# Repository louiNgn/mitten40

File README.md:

# mitten40 
## An ortholinear keyboard with a joystick!

The mitten40 is a 46-key, split-spacebar ortholinear keyboard with a customizable OLED screen and joystick.

### PCB Render

### PCB Layout

### Schematic

# key layout

# firmware
The mitten40 utilizes [QMK firmware](https://qmk.fm/) 

Expect coming changes to C scripts seen in the project, it's untested currently!

# case

The mitten40 utilizes a 3D printed gasket-mount case secured with M3 heat set inserts and screws.

# build guide (TO BE UPDATED ONCE I GET MY HANDS ON IT)
[View bills of materials here!](BOMs)

PCB SMD components: Options include hotplate/hot air soldering at home, assembly by a third-party service (JLCPCB is my choice), or, if you're cracked enough, hand soldering with a soldering iron.

###### FOR THE ASSEMBLY .CSV GO [HERE](production/BOM_PCBAssembly.csv)

|Designator                                                                                                                                                                                                                 |Footprint                              |Quantity|Value                      |LCSC Part #|
|---------------------------------------------------------------------------------------------------------------------------------------------------------------------------------------------------------------------------|---------------------------------------|--------|---------------------------|-----------|
|C1, C2, C3, C5, C8                                                                                                                                                                                                         |402                                    |5       |100nF                      |C60474     |
|C10, C11, C7                                                                                                                                                                                                               |402                                    |3       |1uF                        |C29266     |
|C4, C9                                                                                                                                                                                                                     |402                                    |2       |4.7uF                      |C368809    |
|C6                                                                                                                                                                                                                         |402                                    |1       |10nF                       |C15195     |
|D1, D10, D11, D12, D13, D14, D15, D16, D17, D18, D19, D2, D20, D21, D22, D23, D24, D25, D26, D27, D28, D29, D3, D30, D31, D32, D33, D34, D35, D36, D37, D38, D39, D4, D40, D41, D42, D43, D44, D45, D46, D5, D6, D7, D8, D9|D_SOD-123                              |46      |D                          |C2972760   |
|F1                                                                                                                                                                                                                         |603                                    |1       |500mA                      |C136327    |
|J3                                                                                                                                                                                                                         |USB_C_Receptacle_HCTL_HC-TYPE-C-16P-01A|1       |USB_C_Receptacle_USB2.0_16P|C2765186   |
|R1                                                                                                                                                                                                                         |402                                    |1       |10k                        |C60490     |
|R2, R3                                                                                                                                                                                                                     |402                                    |2       |5.1k                       |C25905     |
|SW0                                                                                                                                                                                                                        |SW_SPST_TL3342                         |1       |SW_Push                    |C2886898   |
|U1                                                                                                                                                                                                                         |LQFP-48_7x7mm_P0.5mm                   |1       |STM32F072CBT6              |C81720     |
|U2                                                                                                                                                                                                                         |SOT-23-6                               |1       |USBLC6-2SC6                |C7519      |
|U3                                                                                                                                                                                                                         |SOT-23-3                               |1       |XC6206P332MR-MS            |C5252899   |

Before continuing, flash QMK firmware on to the keyboard, and use a pair of conductive tweezers to test the PCB for any issues (firmware error, damaged PCB, unresponsive through-hole pins, etc...), and resolve any issues that arises (which may include reordering your PCB).

PCB through-hole components: With sufficient flux and a soldering iron, solder Cherry-MX compatible switches, joystick, and OLED screen through their respective through-hole components. Optionally, solder a 4-pin socket through the OLED screen footprint if you want easily-swappable screens/afraid of damaging the screen when soldering directly.
#### IMPORTANT: REMEMBER TO MOUNT SWITCHES ON TO THE PLATE BEFORE SANDWICHING THEM TO THE PCB AND SOLDERING THEM!!!!

|Designator                                                                                                                                                                                                                 |Part                                   |Quantity|Additional notes           |
|---------------------------------------------------------------------------------------------------------------------------------------------------------------------------------------------------------------------------|---------------------------------------|--------|---------------------------|
|SW1-46                                                                                                                                                                                                                     |MX-Compatible Switches                 |46      |                           |
|SW48                                                                                                                                                                                                                       |PS2-style analog joystick              |1       |Something similar to the [SparkFun joystick](https://www.sparkfun.com/thumb-joystick.html) should work|
|J2                                                                                                                                                                                                                         |0.91" 4-pin OLED Display               |        |Solder sockets on if you want|

Case assembly:
+ Assuming you've mounted the switches on to the plate and the PCB before soldering, begin attaching foam gaskets you've bought on to the top of the small "fins" extruded around the plate on both sides, trimming excess material where necessary to ensure a tight fit.
+ Use your soldering iron, and optionally a heat-set insert press for more precision, push the M3 heat set inserts into their respective holes in the top housing of the keyboard case, before letting everything cool down. (NOTE: DO NOT PRESS TOO FAR AS IT MIGHT GO THROUGH THE ENTIRE HOUSING)
+ Sandwich the PCB-plate between the top and the bottom housing, ensuring the entire contraption is sitting flush in between them.
+ Use M3 screws you've bought to bolt everything together from the bottom housing, tightening it too hard may lead to the housings cracking so please avoid that.
+ Finally, attach the anti-slip nubs on to the bottom of the case in their respective nub holes, and wait for it to set into the PCB before using.

| Part                               | Quantity                  | Additional notes                                                                        | Estimated total costs (may be pricier outside of my country | Links I used |
|------------------------------------|---------------------------|-----------------------------------------------------------------------------------------|-------------------------------------------------------------|--------------|
| Heat-set inserts (M3 * 4 * 4.5)    | 8                         |                                                                                         | $0.60                                                       | [Shopee](https://shopee.vn/30-%E1%BB%90c-c%E1%BA%A5y-nhi%E1%BB%87t-%C4%91%E1%BB%93ng-M1.4-M2-M2.5-M3-M4-M5-M6-T%C3%A1n-Ren-C%E1%BA%A5y-G%E1%BA%AFn-Nh%E1%BB%B1a-Voron-c%E1%BA%A5y-nh%E1%BB%B1a-ecu-c%E1%BA%A5y-%C4%91%E1%BB%93ng-i.213254391.20175149003?extraParams=%7B%22display_model_id%22%3A240042089992%2C%22model_selection_logic%22%3A3%7D)       |
| Threaded Socket Head Cap M3 Screws | 8                         | A shank around 16mm should work, though it *might* go up to 18mm. Proceed with caution. | $0.80                                                       | [Shopee](https://shopee.vn/20C%C3%A1i-Bulong-%E1%BB%91c-Tr%E1%BB%A5-L%E1%BB%A5c-Gi%C3%A1c-trong-M3-M4-M5-M6-M8-inox304-i.801113520.42860368235?extraParams=%7B%22display_model_id%22%3A360010588761%2C%22model_selection_logic%22%3A3%7D&image_ids=vn-11134207-7ras8-mcn8v44lo7z006)       |
| 70mm * 3.5mm * 2mm Poron Foam Gaskets  | 12                        | 2mms of thickness, cut down if need be.                                                 | $6.39                                                            | [Shopee](https://shopee.vn/B%E1%BB%99-5-Mi%E1%BA%BFng-Foam-Gasket-Poron-Thay-Th%E1%BA%BF-Cho-B%C3%A0n-Ph%C3%ADm-C%C6%A1-Gasket-Mount-Yeti-Mech-i.1065372747.46601199338?extraParams=%7B%22display_model_id%22%3A366464970958%2C%22model_selection_logic%22%3A3%7D&image_ids=vn-11134207-81ztc-ms56gdwgudjb02)       |
| 3M SJ5302 Anti-stick nubs          | 4                         |                                                                                         | $1.20                                                       | [Shopee](https://shopee.vn/30-N%C3%BAt-%C4%90%E1%BB%87m-Ch%E1%BB%91ng-v%E1%BB%A1-%C4%90i%E1%BB%87n-Tho%E1%BA%A1i-3M-SJ5302-(N%C3%BAt-V%C3%B2m-C%E1%BA%A7u)-v%C3%A0-20-N%C3%BAt-JS5312-(N%C3%BAt-D%E1%BA%B9t)-i.13893035.2055224981?extraParams=%7B%22display_model_id%22%3A223329961555%2C%22model_selection_logic%22%3A3%7D)       |
| Filament (PLA)                     | ~270+ grams or ~90m (PLA) | May vary with different filaments and print settings                                    | ~$5.40                                                      | Self-funded and printed (I have a lot of filament lying around)             |

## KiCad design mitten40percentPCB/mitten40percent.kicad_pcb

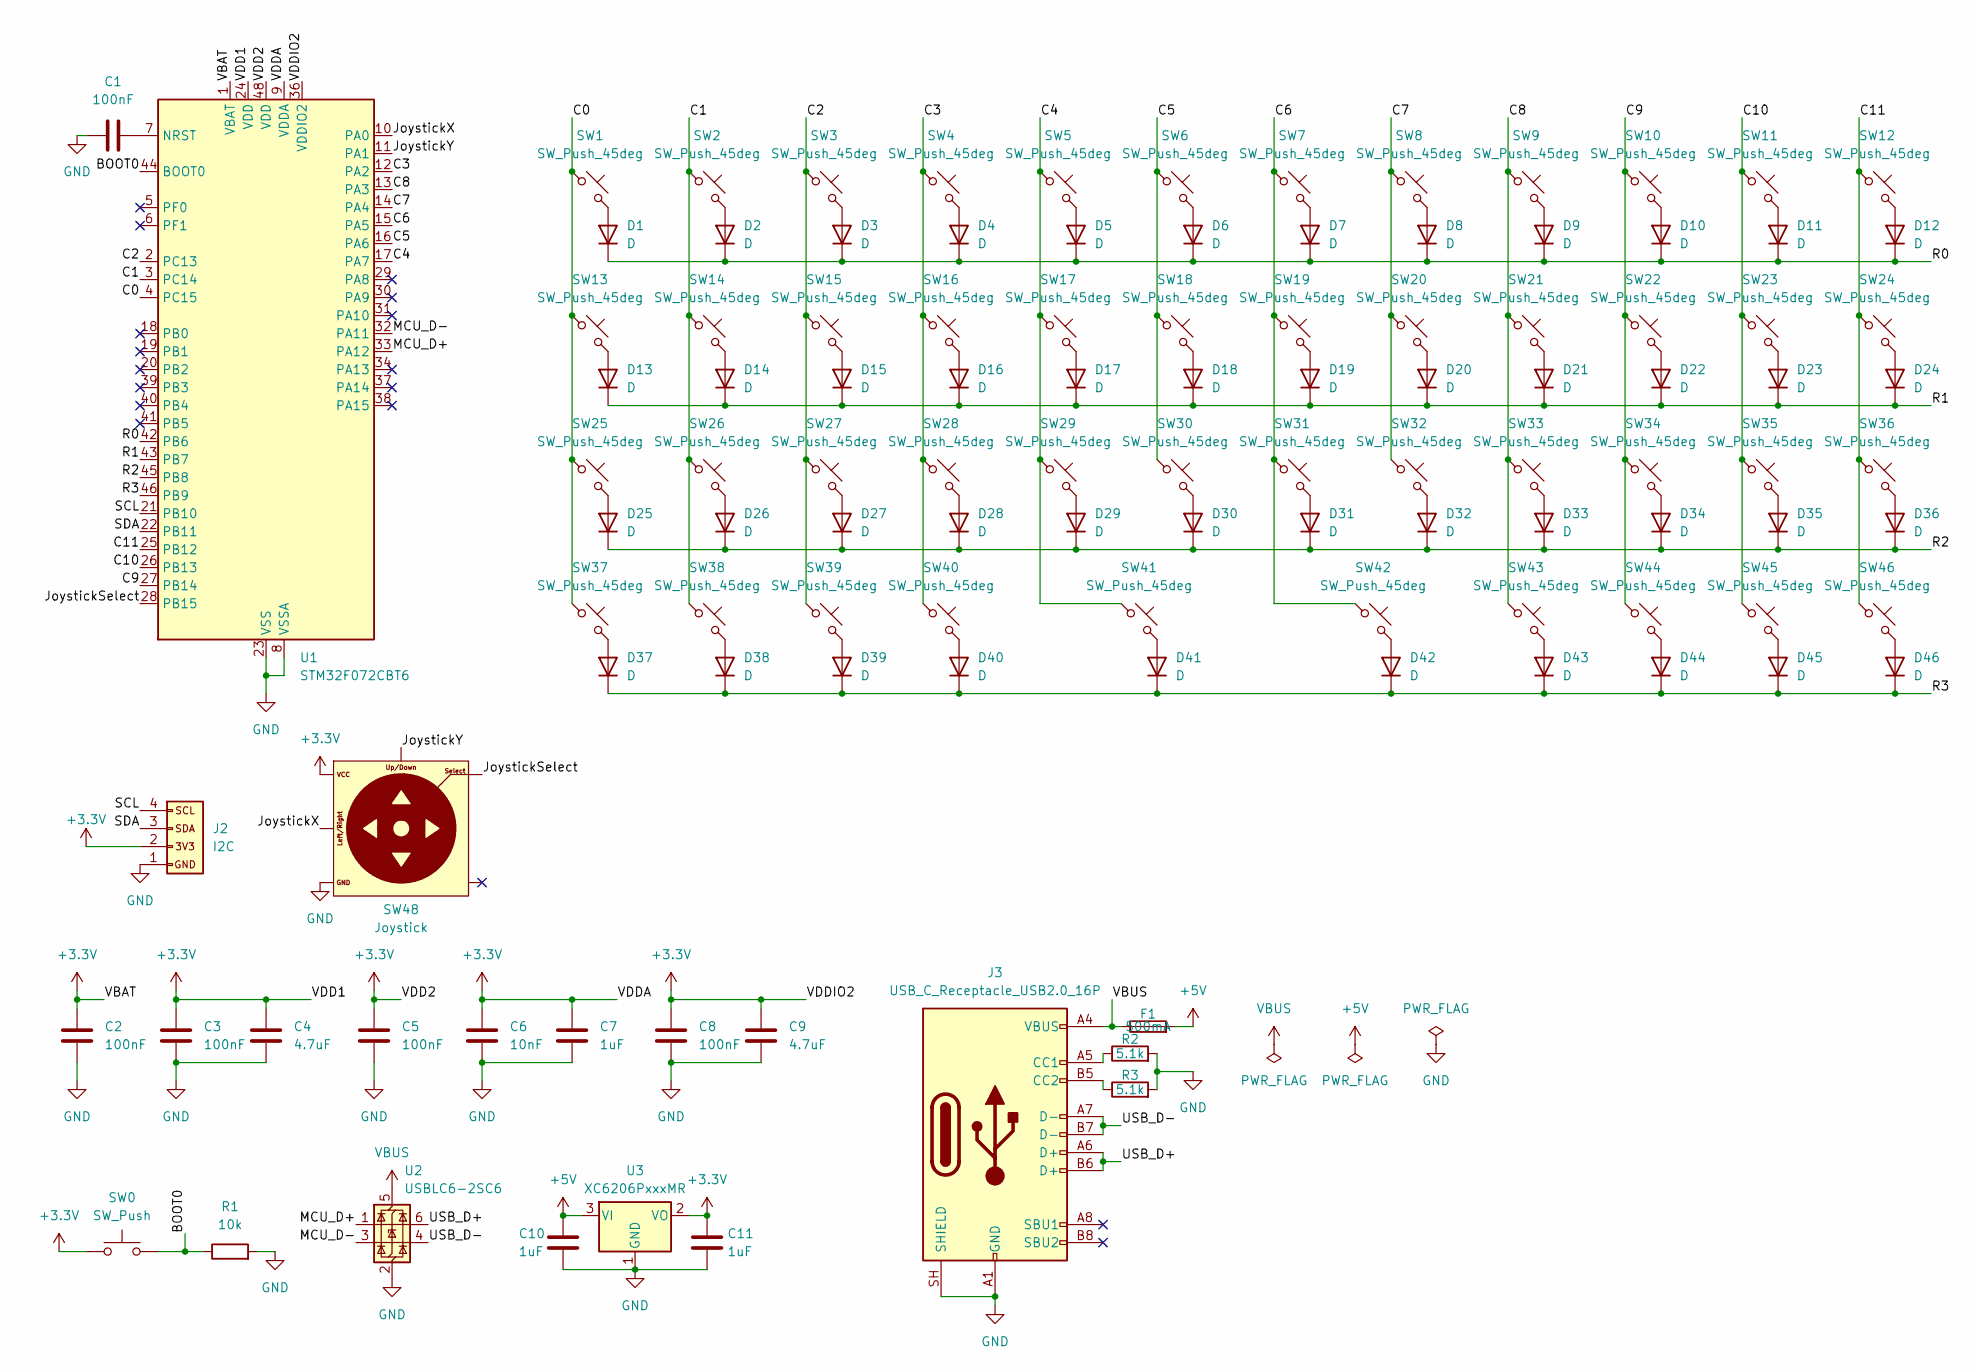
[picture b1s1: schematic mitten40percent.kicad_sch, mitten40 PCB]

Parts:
C1, C2, C3, C5, C8: 100nF; C_0402_1005Metric
C4, C9: 4.7uF; C_0402_1005Metric
C6: 10nF; C_0402_1005Metric
C7, C10, C11: 1uF; C_0402_1005Metric
D1, D2, D3, D4, D5, D6, D7, D8, D9, D10, D11, D12, D13, D14, D15, D16, D17, D18, D19, D20, D21, D22, D23, D24, D25, D26, D27, D28, D29, D30, D31, D32, D33, D34, D35, D36, D37, D38, D39, D40, D41, D42, D43, D44, D45, D46: D; D_SOD-123
F1: 500mA; Fuse_0603_1608Metric
J2: I2C; ER_OLEDM0.91_1x-I2C
J3: USB_C_Receptacle_USB2.0_16P; USB_C_Receptacle_HCTL_HC-TYPE-C-16P-01A
R1: 10k; R_0402_1005Metric
R2, R3: 5.1k; R_0402_1005Metric
SW0: SW_Push; SW_SPST_TL3342
SW1, SW2, SW3, SW4, SW5, SW6, SW7, SW8, SW9, SW10, SW11, SW12, SW13, SW14, SW15, SW16, SW17, SW18, SW19, SW20, SW21, SW22, SW23, SW24, SW25, SW26, SW27, SW28, SW29, SW30, SW31, SW32, SW33, SW34, SW35, SW36, SW37, SW38, SW39, SW40, SW43, SW44, SW45, SW46: SW_Push_45deg; SW_Cherry_MX_1.00u_PCB
SW41, SW42: SW_Push_45deg; SW_Cherry_MX_2.00u_PCB
SW48: Joystick; Joystick_PTH
U1: STM32F072CBT6; LQFP-48_7x7mm_P0.5mm
U2: USBLC6-2SC6; SOT-23-6
U3: XC6206PxxxMR; SOT-23-3

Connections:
+3.3V: C2.1, C3.1, C4.1, C5.1, C6.1, C7.1, C8.1, C9.1, C11.1, J2.2, SW0.1, SW48.VCC, U1.1 (VBAT), U1.9 (VDDA), U1.24 (VDD), U1.36 (VDDIO2), U1.48 (VDD), U3.2 (VO)
+5V: C10.1, F1.2, U3.3 (VI)
/BOOT0: R1.1, SW0.2, U1.44 (BOOT0)
/C0: SW1.1, SW13.1, SW25.1, SW37.1, U1.4 (PC15)
/C1: SW2.1, SW14.1, SW26.1, SW38.1, U1.3 (PC14)
/C2: SW3.1, SW15.1, SW27.1, SW39.1, U1.2 (PC13)
/C3: SW4.1, SW16.1, SW28.1, SW40.1, U1.12 (PA2)
/C4: SW5.1, SW17.1, SW29.1, SW41.1, U1.17 (PA7)
/C5: SW6.1, SW18.1, SW30.1, U1.16 (PA6)
/C6: SW7.1, SW19.1, SW31.1, SW42.1, U1.15 (PA5)
/C7: SW8.1, SW20.1, SW32.1, U1.14 (PA4)
/C8: SW9.1, SW21.1, SW33.1, SW43.1, U1.13 (PA3)
/C9: SW10.1, SW22.1, SW34.1, SW44.1, U1.27 (PB14)
/C10: SW11.1, SW23.1, SW35.1, SW45.1, U1.26 (PB13)
/C11: SW12.1, SW24.1, SW36.1, SW46.1, U1.25 (PB12)
/JoystickSelect: SW48.Select, U1.28 (PB15)
/JoystickX: SW48.Horizontal, U1.10 (PA0)
/JoystickY: SW48.Vertical, U1.11 (PA1)
/MCU_D+: U1.33 (PA12), U2.1 (I/O1)
/MCU_D-: U1.32 (PA11), U2.3 (I/O2)
/R0: D1.1 (K), D2.1 (K), D3.1 (K), D4.1 (K), D5.1 (K), D6.1 (K), D7.1 (K), D8.1 (K), D9.1 (K), D10.1 (K), D11.1 (K), D12.1 (K), U1.42 (PB6)
/R1: D13.1 (K), D14.1 (K), D15.1 (K), D16.1 (K), D17.1 (K), D18.1 (K), D19.1 (K), D20.1 (K), D21.1 (K), D22.1 (K), D23.1 (K), D24.1 (K), U1.43 (PB7)
/R2: D25.1 (K), D26.1 (K), D27.1 (K), D28.1 (K), D29.1 (K), D30.1 (K), D31.1 (K), D32.1 (K), D33.1 (K), D34.1 (K), D35.1 (K), D36.1 (K), U1.45 (PB8)
/R3: D37.1 (K), D38.1 (K), D39.1 (K), D40.1 (K), D41.1 (K), D42.1 (K), D43.1 (K), D44.1 (K), D45.1 (K), D46.1 (K), U1.46 (PB9)
/SCL: J2.4, U1.21 (PB10)
/SDA: J2.3, U1.22 (PB11)
/USB_D+: J3.A6 (D+), J3.B6 (D+), U2.6 (I/O1)
/USB_D-: J3.A7 (D-), J3.B7 (D-), U2.4 (I/O2)
GND: C1.1, C2.2, C3.2, C4.2, C5.2, C6.2, C7.2, C8.2, C9.2, C10.2, C11.2, J2.1, J3.A1 (GND), J3.A12 (GND), J3.B1 (GND), J3.B12 (GND), J3.SH (SHIELD), R1.2, R2.2, R3.2, SW48.GND, U1.8 (VSSA), U1.23 (VSS), U1.35 (VSS), U1.47 (VSS), U2.2 (GND), U3.1 (GND)
unnamed: D1.2 (A), SW1.2
unnamed: D2.2 (A), SW2.2
unnamed: D3.2 (A), SW3.2
unnamed: D4.2 (A), SW4.2
unnamed: D5.2 (A), SW5.2
unnamed: D6.2 (A), SW6.2
unnamed: D7.2 (A), SW7.2
unnamed: D8.2 (A), SW8.2
unnamed: D9.2 (A), SW9.2
unnamed: D10.2 (A), SW10.2
unnamed: D11.2 (A), SW11.2
unnamed: D12.2 (A), SW12.2
unnamed: D13.2 (A), SW13.2
unnamed: D14.2 (A), SW14.2
unnamed: D15.2 (A), SW15.2
unnamed: D16.2 (A), SW16.2
unnamed: D17.2 (A), SW17.2
unnamed: D18.2 (A), SW18.2
unnamed: D19.2 (A), SW19.2
unnamed: D20.2 (A), SW20.2
unnamed: D21.2 (A), SW21.2
unnamed: D22.2 (A), SW22.2
unnamed: D23.2 (A), SW23.2
unnamed: D24.2 (A), SW24.2
unnamed: D25.2 (A), SW25.2
unnamed: D26.2 (A), SW26.2
unnamed: D27.2 (A), SW27.2
unnamed: D28.2 (A), SW28.2
unnamed: D29.2 (A), SW29.2
unnamed: D30.2 (A), SW30.2
unnamed: D31.2 (A), SW31.2
unnamed: D32.2 (A), SW32.2
unnamed: D33.2 (A), SW33.2
unnamed: D34.2 (A), SW34.2
unnamed: D35.2 (A), SW35.2
unnamed: D36.2 (A), SW36.2
unnamed: D37.2 (A), SW37.2
unnamed: D38.2 (A), SW38.2
unnamed: D39.2 (A), SW39.2
unnamed: D40.2 (A), SW40.2
unnamed: D41.2 (A), SW41.2
unnamed: D42.2 (A), SW42.2
unnamed: D43.2 (A), SW43.2
unnamed: D44.2 (A), SW44.2
unnamed: D45.2 (A), SW45.2
unnamed: D46.2 (A), SW46.2
unnamed: J3.A5 (CC1), R2.1
unnamed: J3.B5 (CC2), R3.1
unnamed: C1.2, U1.7 (NRST)
VBUS: F1.1, J3.A4 (VBUS), J3.A9 (VBUS), J3.B4 (VBUS), J3.B9 (VBUS), U2.5 (VBUS)

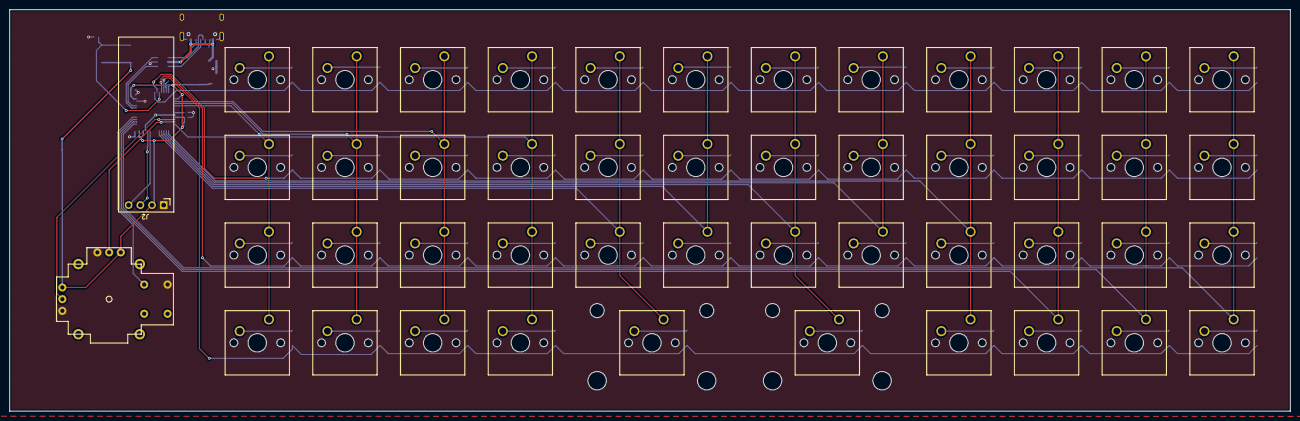
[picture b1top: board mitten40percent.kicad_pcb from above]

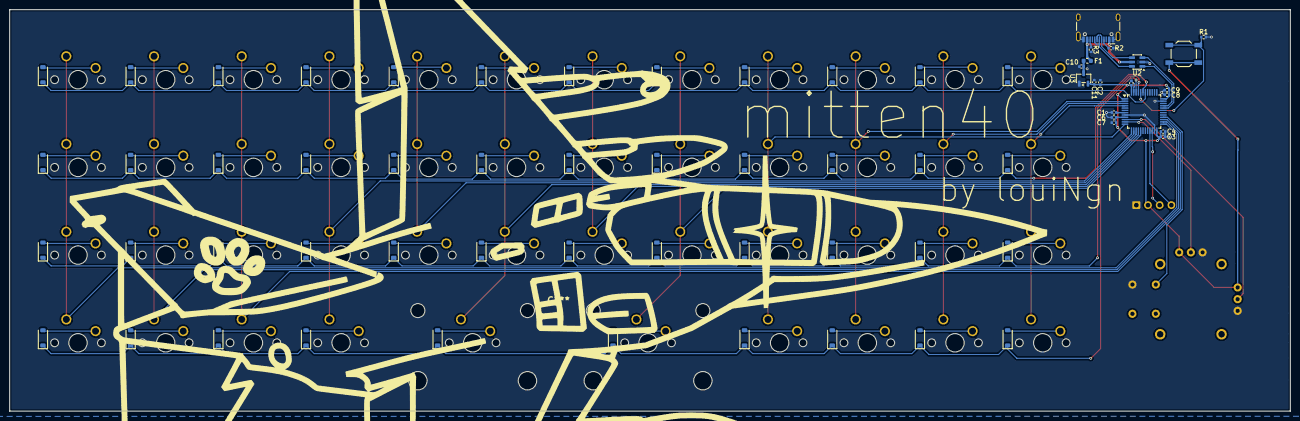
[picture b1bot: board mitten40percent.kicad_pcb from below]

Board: 2 copper layers, 278.2 x 87.2 mm, 114 parts (66 on the bottom side), 79 nets.

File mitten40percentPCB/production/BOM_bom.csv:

Designator,Footprint,Quantity,Value,LCSC Part #
"C1, C2, C3, C5, C8",0402,5,100nF,
"C10, C11, C7",0402,3,1uF,
"C4, C9",0402,2,4.7uF,
C6,0402,1,10nF,
"D1, D10, D11, D12, D13, D14, D15, D16, D17, D18, D19, D2, D20, D21, D22, D23, D24, D25, D26, D27, D28, D29, D3, D30, D31, D32, D33, D34, D35, D36, D37, D38, D39, D4, D40, D41, D42, D43, D44, D45, D46, D5, D6, D7, D8, D9",D_SOD-123,46,D,
F1,0603,1,500mA,
J2,ER_OLEDM0.91_1x-I2C,1,I2C,
J3,USB_C_Receptacle_HCTL_HC-TYPE-C-16P-01A,1,USB_C_Receptacle_USB2.0_16P,
R1,0402,1,10k,
"R2, R3",0402,2,5.1k,
SW0,SW_SPST_TL3342,1,SW_Push,
"SW1, SW10, SW11, SW12, SW13, SW14, SW15, SW16, SW17, SW18, SW19, SW2, SW20, SW21, SW22, SW23, SW24, SW25, SW26, SW27, SW28, SW29, SW3, SW30, SW31, SW32, SW33, SW34, SW35, SW36, SW37, SW38, SW39, SW4, SW40, SW43, SW44, SW45, SW46, SW5, SW6, SW7, SW8, SW9",SW_Cherry_MX_1.00u_PCB,44,SW_Push_45deg,
"SW41, SW42",SW_Cherry_MX_2.00u_PCB,2,SW_Push_45deg,
SW48,Joystick_PTH,1,Joystick,
U1,LQFP-48_7x7mm_P0.5mm,1,STM32F072CBT6,
U2,SOT-23-6,1,USBLC6-2SC6,
U3,SOT-23-3,1,XC6206PxxxMR,
